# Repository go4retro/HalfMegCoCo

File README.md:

# HalfMegCoCo - an SRAM-based 512kB RAM Expansion for the TANDY Color Computer 3
This printed circuit board implements a very simplistic SRAM-based memory expansion for the Color Computer 3.  All parts are through hole for easy hobbyist assembly. If 512kB x 8 SRAMs are utilized, the unit offers 1MB of RAM expansion, but requires a DAT board from either Boysontech or Cloud9 to utilize the upper 512kB.

## License
Copyright (C) 2020  RETRO Innovations

These files are free designs; you can redistribute them and/or modify
them under the terms of the Creative Commons Attribution-ShareAlike 
4.0 International License.

You should have received a copy of the license along with this
work. If not, see <http://creativecommons.org/licenses/by-sa/4.0/>.

These files are distributed in the hope that they will be useful,
but WITHOUT ANY WARRANTY; without even the implied warranty of
MERCHANTABILITY or FITNESS FOR A PARTICULAR PURPOSE.  See the
license for more details.

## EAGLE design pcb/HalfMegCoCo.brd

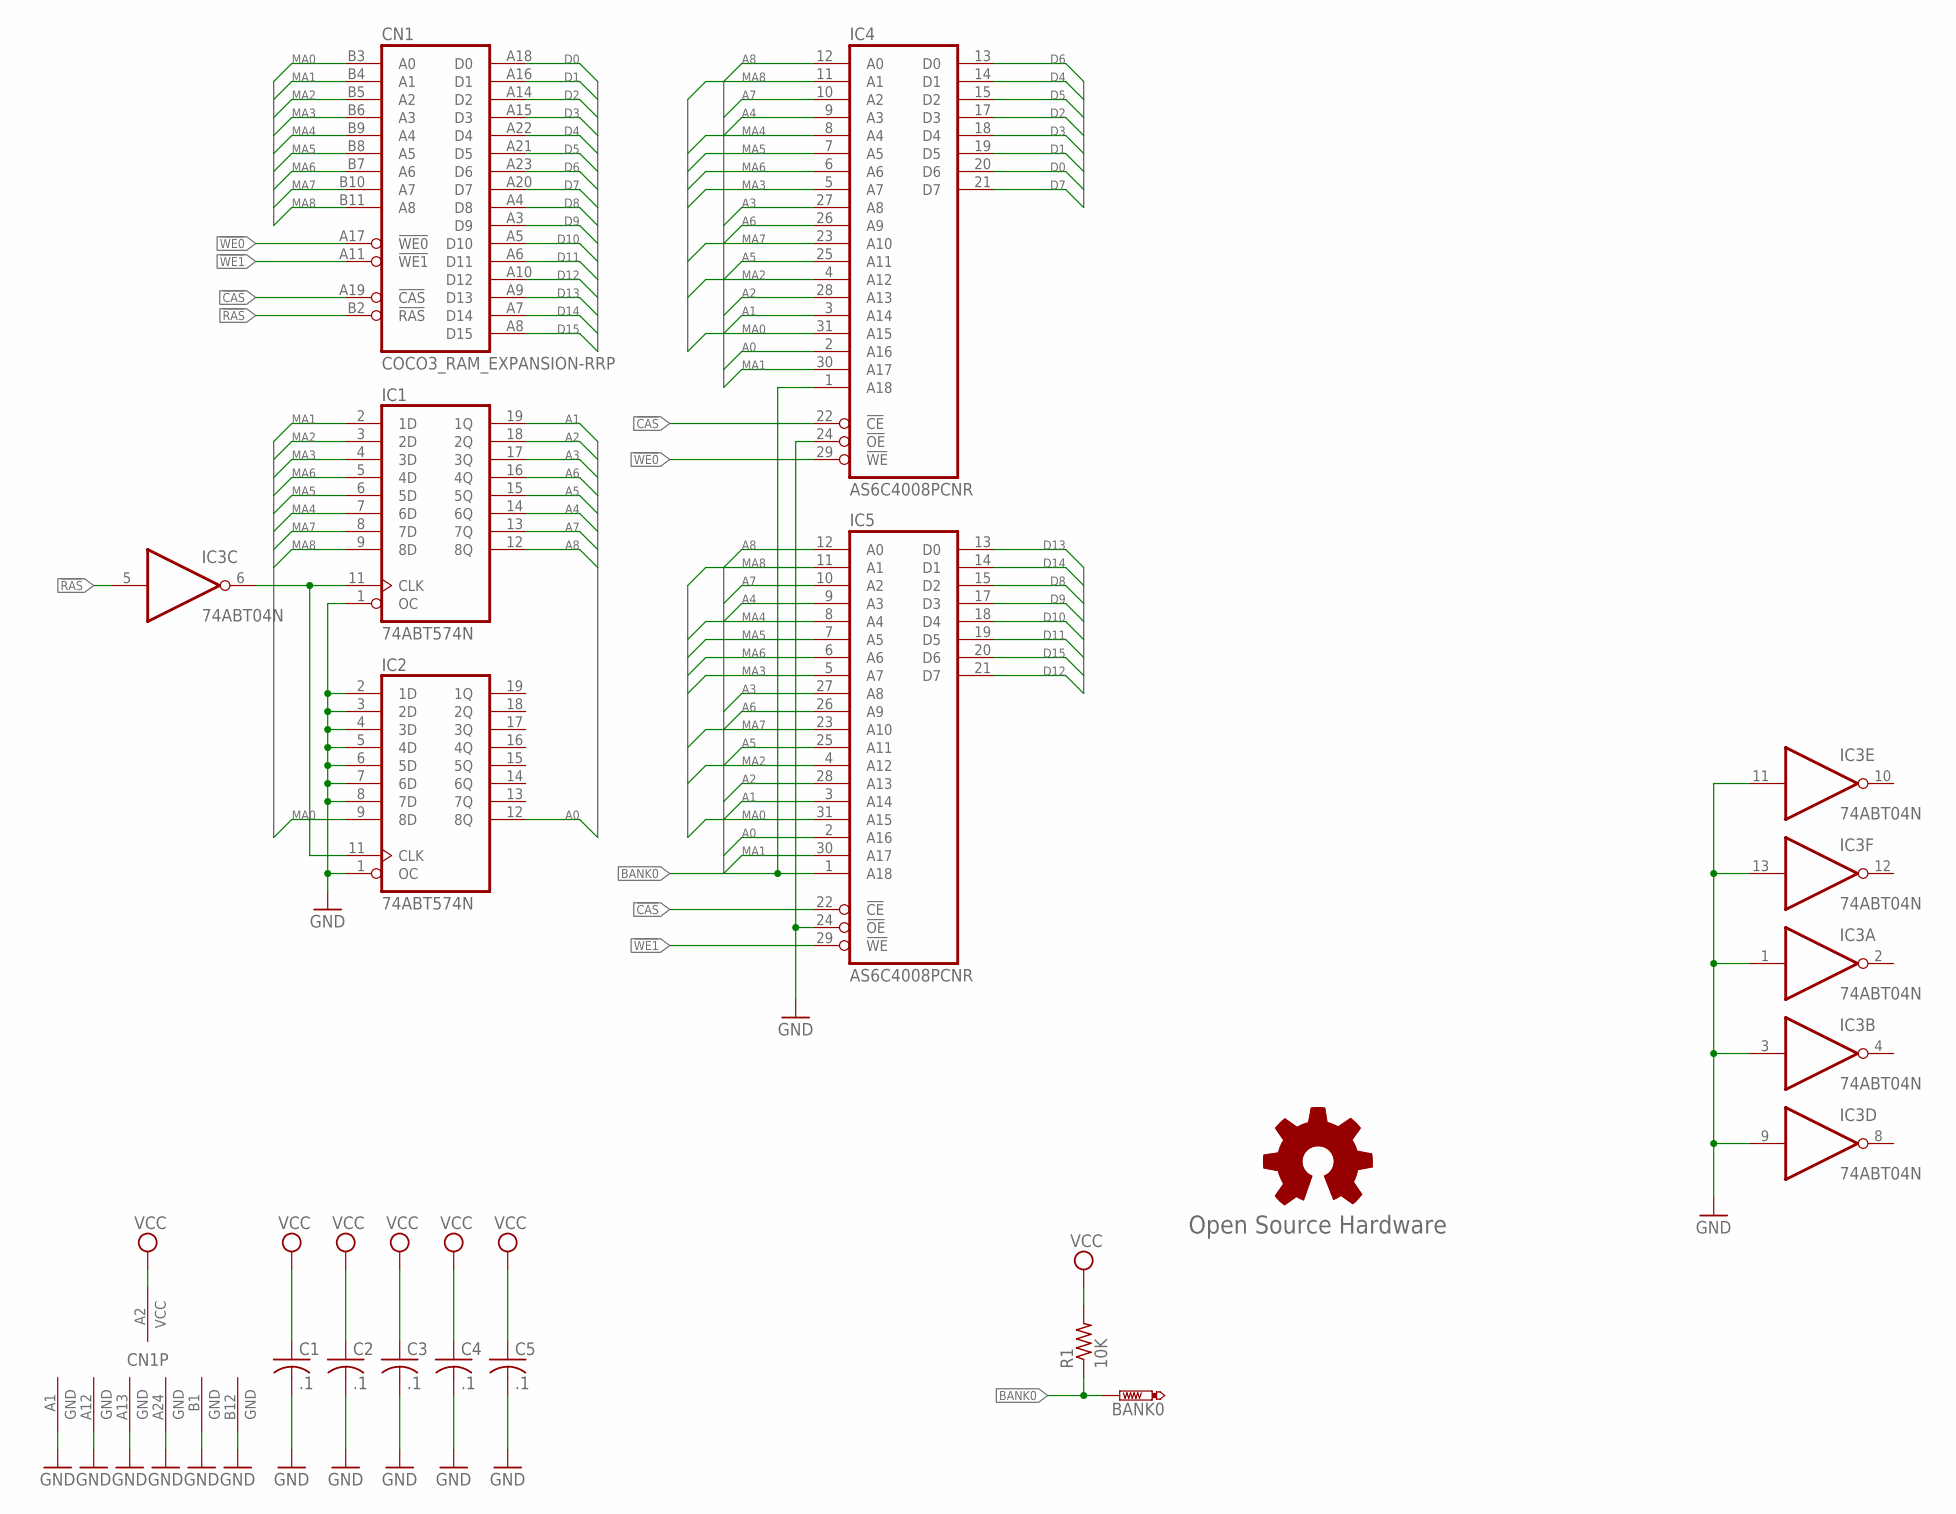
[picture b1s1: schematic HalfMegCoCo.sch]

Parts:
BANK0: PTR1PAD1-13; P1-13
C1, C2, C3, C4, C5: .1; C025-025X050
CN1: COCO3_RAM_EXPANSION-RRP; RAM_EXPANSION_REV_RP
GOLD_ORB_SM1: Open Source Hardware; OSHW_8MM
IC1, IC2: 74ABT574N; DIL20-RP
IC3: 74ABT04N; DIL14-RP
IC4, IC5: AS6C4008PCNR; DIL32-RP
R1: 10K; 0204/7

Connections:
!CAS: CN1.A19 (!CAS), IC4.22 (!CE), IC5.22 (!CE)
!RAS: CN1.B2 (!RAS), IC3.5 (I)
!WE0: CN1.A17 (!WE0), IC4.29 (!WE)
!WE1: CN1.A11 (!WE1), IC5.29 (!WE)
A0: IC2.12 (8Q), IC4.2 (A16), IC5.2 (A16)
A1: IC1.19 (1Q), IC4.3 (A14), IC5.3 (A14)
A2: IC1.18 (2Q), IC4.28 (A13), IC5.28 (A13)
A3: IC1.17 (3Q), IC4.27 (A8), IC5.27 (A8)
A4: IC1.14 (6Q), IC4.9 (A3), IC5.9 (A3)
A5: IC1.15 (5Q), IC4.25 (A11), IC5.25 (A11)
A6: IC1.16 (4Q), IC4.26 (A9), IC5.26 (A9)
A7: IC1.13 (7Q), IC4.10 (A2), IC5.10 (A2)
A8: IC1.12 (8Q), IC4.12 (A0), IC5.12 (A0)
BANK0: BANK0.TP, IC4.1 (A18), IC5.1 (A18), R1.1
D0: CN1.A18 (D0), IC4.20 (D6)
D1: CN1.A16 (D1), IC4.19 (D5)
D2: CN1.A14 (D2), IC4.17 (D3)
D3: CN1.A15 (D3), IC4.18 (D4)
D4: CN1.A22 (D4), IC4.14 (D1)
D5: CN1.A21 (D5), IC4.15 (D2)
D6: CN1.A23 (D6), IC4.13 (D0)
D7: CN1.A20 (D7), IC4.21 (D7)
D8: CN1.A4 (D8), IC5.15 (D2)
D9: CN1.A3 (D9), IC5.17 (D3)
D10: CN1.A5 (D10), IC5.18 (D4)
D11: CN1.A6 (D11), IC5.19 (D5)
D12: CN1.A10 (D12), IC5.21 (D7)
D13: CN1.A9 (D13), IC5.13 (D0)
D14: CN1.A7 (D14), IC5.14 (D1)
D15: CN1.A8 (D15), IC5.20 (D6)
GND: C1.2, C2.2, C3.2, C4.2, C5.2, CN1.A1 (GND), CN1.A12 (GND), CN1.A13 (GND), CN1.A24 (GND), CN1.B1 (GND), CN1.B12 (GND), IC1.1 (OC), IC1.10 (GND), IC2.1 (OC), IC2.2 (1D), IC2.3 (2D), IC2.4 (3D), IC2.5 (4D), IC2.6 (5D), IC2.7 (6D), IC2.8 (7D), IC2.10 (GND), IC3.1 (I), IC3.3 (I), IC3.7 (GND), IC3.9 (I), IC3.11 (I), IC3.13 (I), IC4.16 (GND), IC4.24 (!OE), IC5.16 (GND), IC5.24 (!OE)
MA0: CN1.B3 (A0), IC2.9 (8D), IC4.31 (A15), IC5.31 (A15)
MA1: CN1.B4 (A1), IC1.2 (1D), IC4.30 (A17), IC5.30 (A17)
MA2: CN1.B5 (A2), IC1.3 (2D), IC4.4 (A12), IC5.4 (A12)
MA3: CN1.B6 (A3), IC1.4 (3D), IC4.5 (A7), IC5.5 (A7)
MA4: CN1.B9 (A4), IC1.7 (6D), IC4.8 (A4), IC5.8 (A4)
MA5: CN1.B8 (A5), IC1.6 (5D), IC4.7 (A5), IC5.7 (A5)
MA6: CN1.B7 (A6), IC1.5 (4D), IC4.6 (A6), IC5.6 (A6)
MA7: CN1.B10 (A7), IC1.8 (7D), IC4.23 (A10), IC5.23 (A10)
MA8: CN1.B11 (A8), IC1.9 (8D), IC4.11 (A1), IC5.11 (A1)
unnamed: IC1.11 (CLK), IC2.11 (CLK), IC3.6 (O)
VCC: C1.1, C2.1, C3.1, C4.1, C5.1, CN1.A2 (VCC), IC1.20 (VCC), IC2.20 (VCC), IC3.14 (VCC), IC4.32 (VCC), IC5.32 (VCC), R1.2

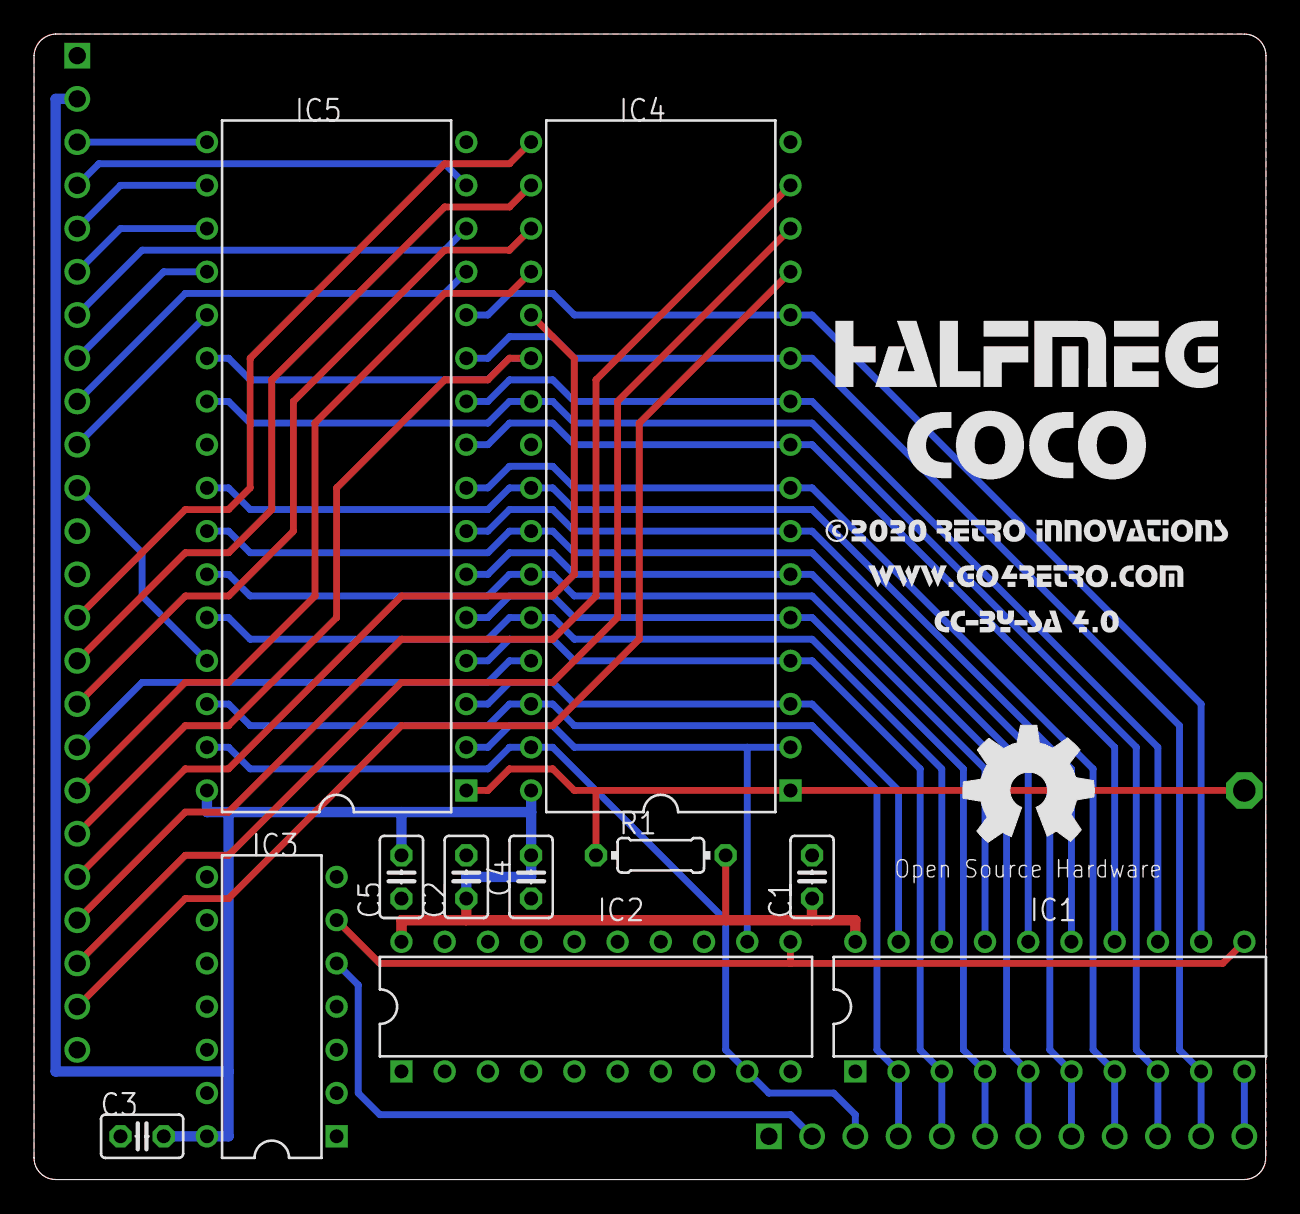
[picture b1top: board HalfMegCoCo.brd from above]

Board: 2 copper layers, 72.4 x 67.3 mm, 14 parts (0 on the bottom side), 42 nets.

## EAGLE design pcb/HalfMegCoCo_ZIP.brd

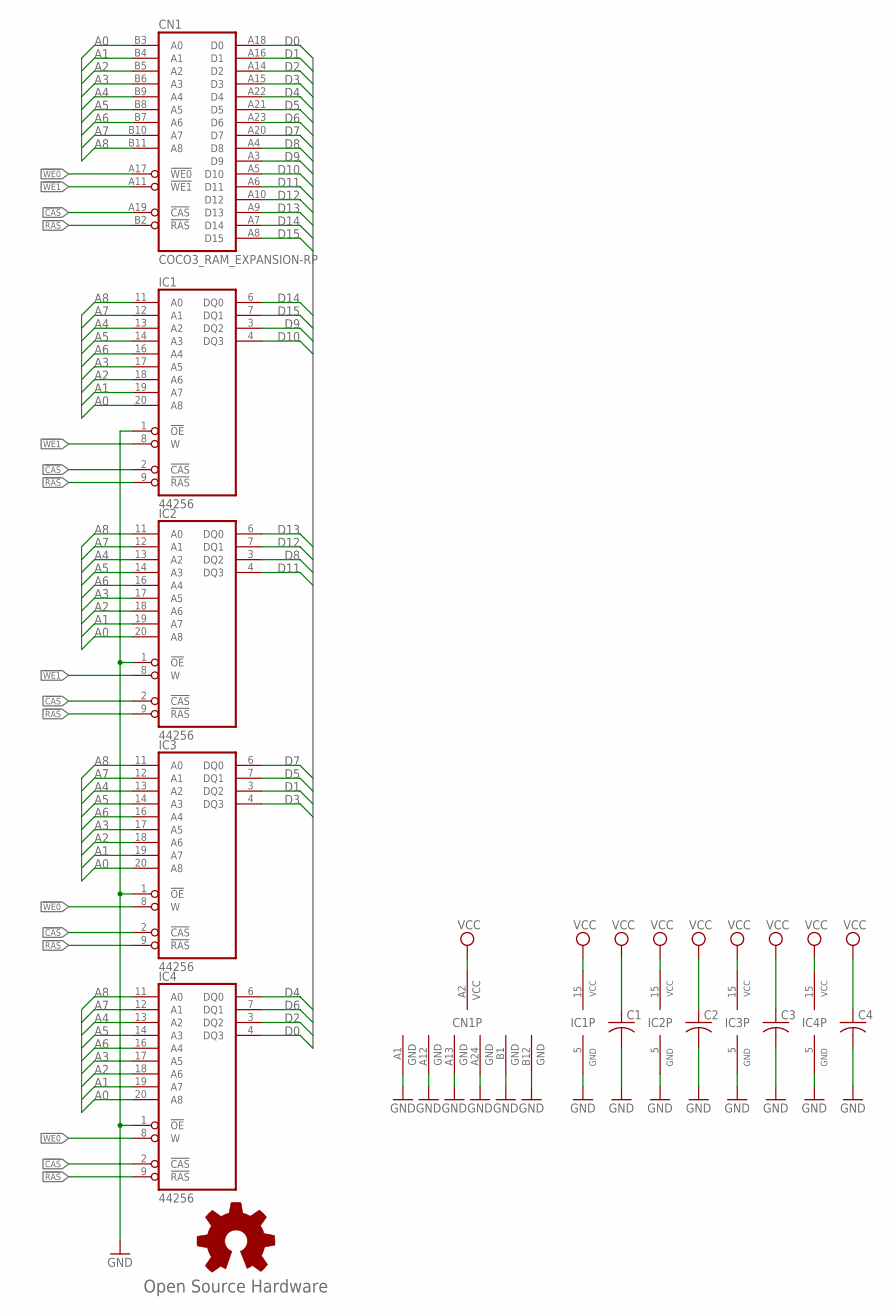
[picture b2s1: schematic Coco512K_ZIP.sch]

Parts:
C1, C2, C3, C4: C-US025-025X050; C025-025X050
CN1: COCO3_RAM_EXPANSION-RP; RAM_EXPANSION-RP
GOLD_ORB_SM1: Open Source Hardware; OSHW_8MM
IC1, IC2, IC3, IC4: 44256; ZIP20

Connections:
!CAS: CN1.A19 (!CAS), IC1.2 (!CAS), IC2.2 (!CAS), IC3.2 (!CAS), IC4.2 (!CAS)
!RAS: CN1.B2 (!RAS), IC1.9 (!RAS), IC2.9 (!RAS), IC3.9 (!RAS), IC4.9 (!RAS)
!WE0: CN1.A17 (!WE0), IC3.8 (W), IC4.8 (W)
!WE1: CN1.A11 (!WE1), IC1.8 (W), IC2.8 (W)
A0: CN1.B3 (A0), IC1.20 (A8), IC2.20 (A8), IC3.20 (A8), IC4.20 (A8)
A1: CN1.B4 (A1), IC1.19 (A7), IC2.19 (A7), IC3.19 (A7), IC4.19 (A7)
A2: CN1.B5 (A2), IC1.18 (A6), IC2.18 (A6), IC3.18 (A6), IC4.18 (A6)
A3: CN1.B6 (A3), IC1.17 (A5), IC2.17 (A5), IC3.17 (A5), IC4.17 (A5)
A4: CN1.B9 (A4), IC1.13 (A2), IC2.13 (A2), IC3.13 (A2), IC4.13 (A2)
A5: CN1.B8 (A5), IC1.14 (A3), IC2.14 (A3), IC3.14 (A3), IC4.14 (A3)
A6: CN1.B7 (A6), IC1.16 (A4), IC2.16 (A4), IC3.16 (A4), IC4.16 (A4)
A7: CN1.B10 (A7), IC1.12 (A1), IC2.12 (A1), IC3.12 (A1), IC4.12 (A1)
A8: CN1.B11 (A8), IC1.11 (A0), IC2.11 (A0), IC3.11 (A0), IC4.11 (A0)
D0: CN1.A18 (D0), IC4.4 (DQ3)
D1: CN1.A16 (D1), IC3.3 (DQ2)
D2: CN1.A14 (D2), IC4.3 (DQ2)
D3: CN1.A15 (D3), IC3.4 (DQ3)
D4: CN1.A22 (D4), IC4.6 (DQ0)
D5: CN1.A21 (D5), IC3.7 (DQ1)
D6: CN1.A23 (D6), IC4.7 (DQ1)
D7: CN1.A20 (D7), IC3.6 (DQ0)
D8: CN1.A4 (D8), IC2.3 (DQ2)
D9: CN1.A3 (D9), IC1.3 (DQ2)
D10: CN1.A5 (D10), IC1.4 (DQ3)
D11: CN1.A6 (D11), IC2.4 (DQ3)
D12: CN1.A10 (D12), IC2.7 (DQ1)
D13: CN1.A9 (D13), IC2.6 (DQ0)
D14: CN1.A7 (D14), IC1.6 (DQ0)
D15: CN1.A8 (D15), IC1.7 (DQ1)
GND: C1.2, C2.2, C3.2, C4.2, CN1.A1 (GND), CN1.A12 (GND), CN1.A13 (GND), CN1.A24 (GND), CN1.B1 (GND), CN1.B12 (GND), IC1.1 (!OE), IC1.5 (GND), IC2.1 (!OE), IC2.5 (GND), IC3.1 (!OE), IC3.5 (GND), IC4.1 (!OE), IC4.5 (GND)
VCC: C1.1, C2.1, C3.1, C4.1, CN1.A2 (VCC), IC1.15 (VCC), IC2.15 (VCC), IC3.15 (VCC), IC4.15 (VCC)

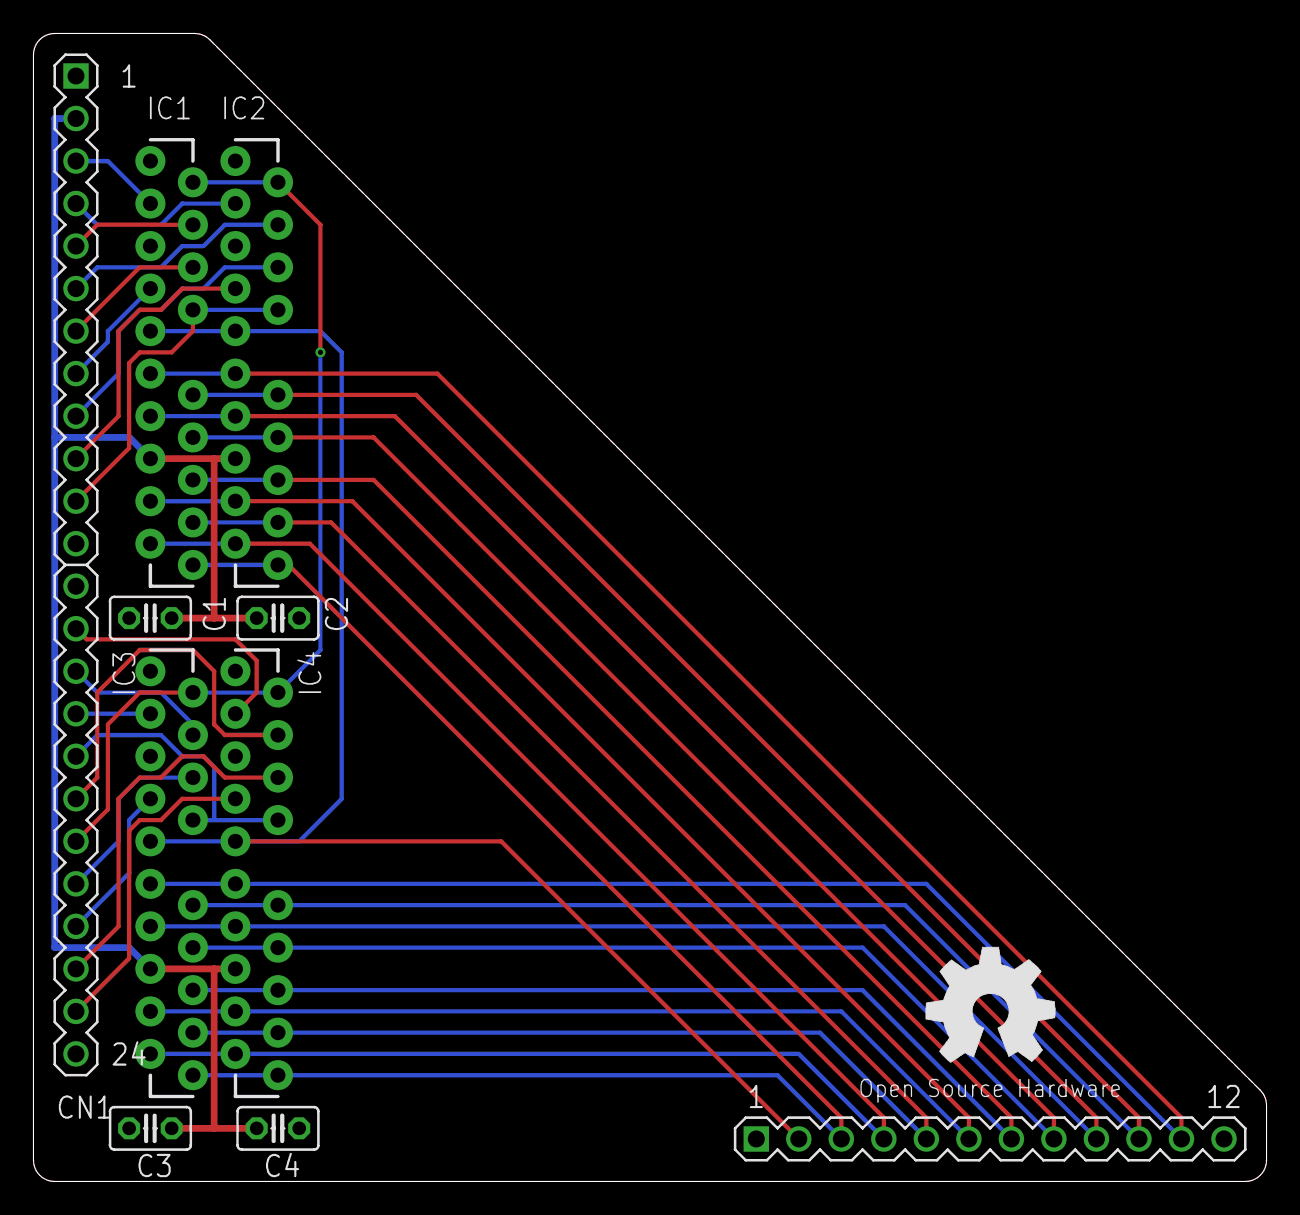
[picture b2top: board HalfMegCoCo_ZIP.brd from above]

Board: 2 copper layers, 73.7 x 68.6 mm, 10 parts (0 on the bottom side), 31 nets.

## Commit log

2020-03-03 Fixed filename
2020-05-25 SRAM-based version added, DRAM version removed.
2020-05-25 Cleaned up Copyright bitmap files
2020-05-25 fix typo in README.md
